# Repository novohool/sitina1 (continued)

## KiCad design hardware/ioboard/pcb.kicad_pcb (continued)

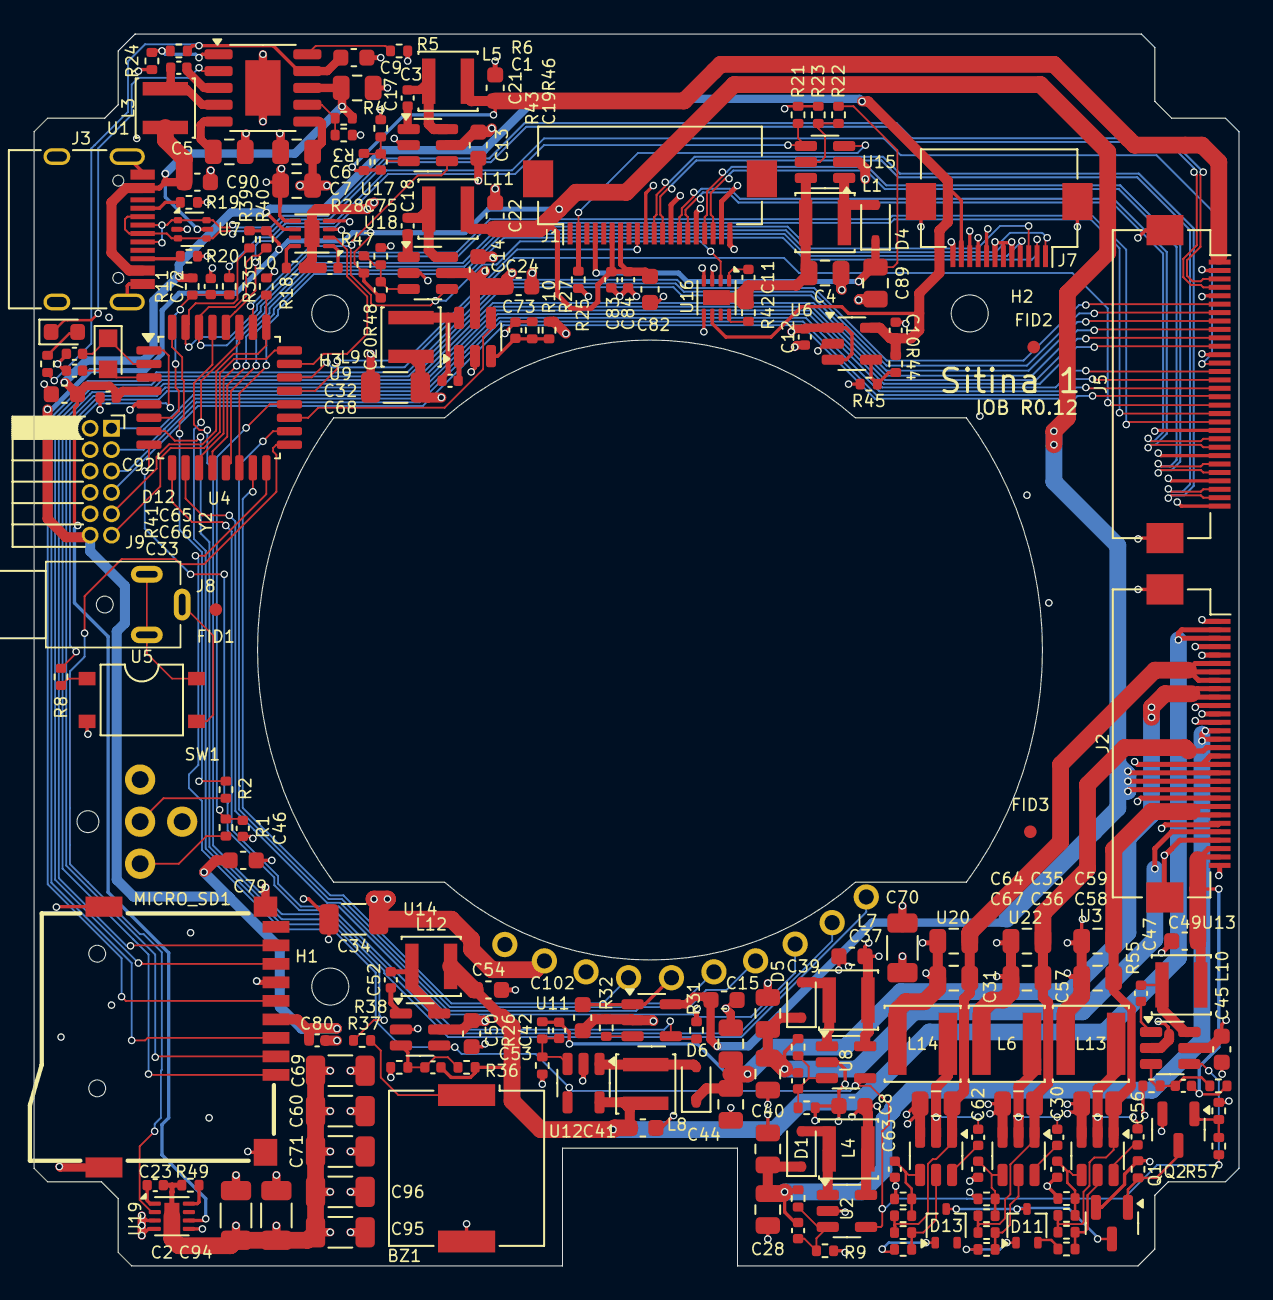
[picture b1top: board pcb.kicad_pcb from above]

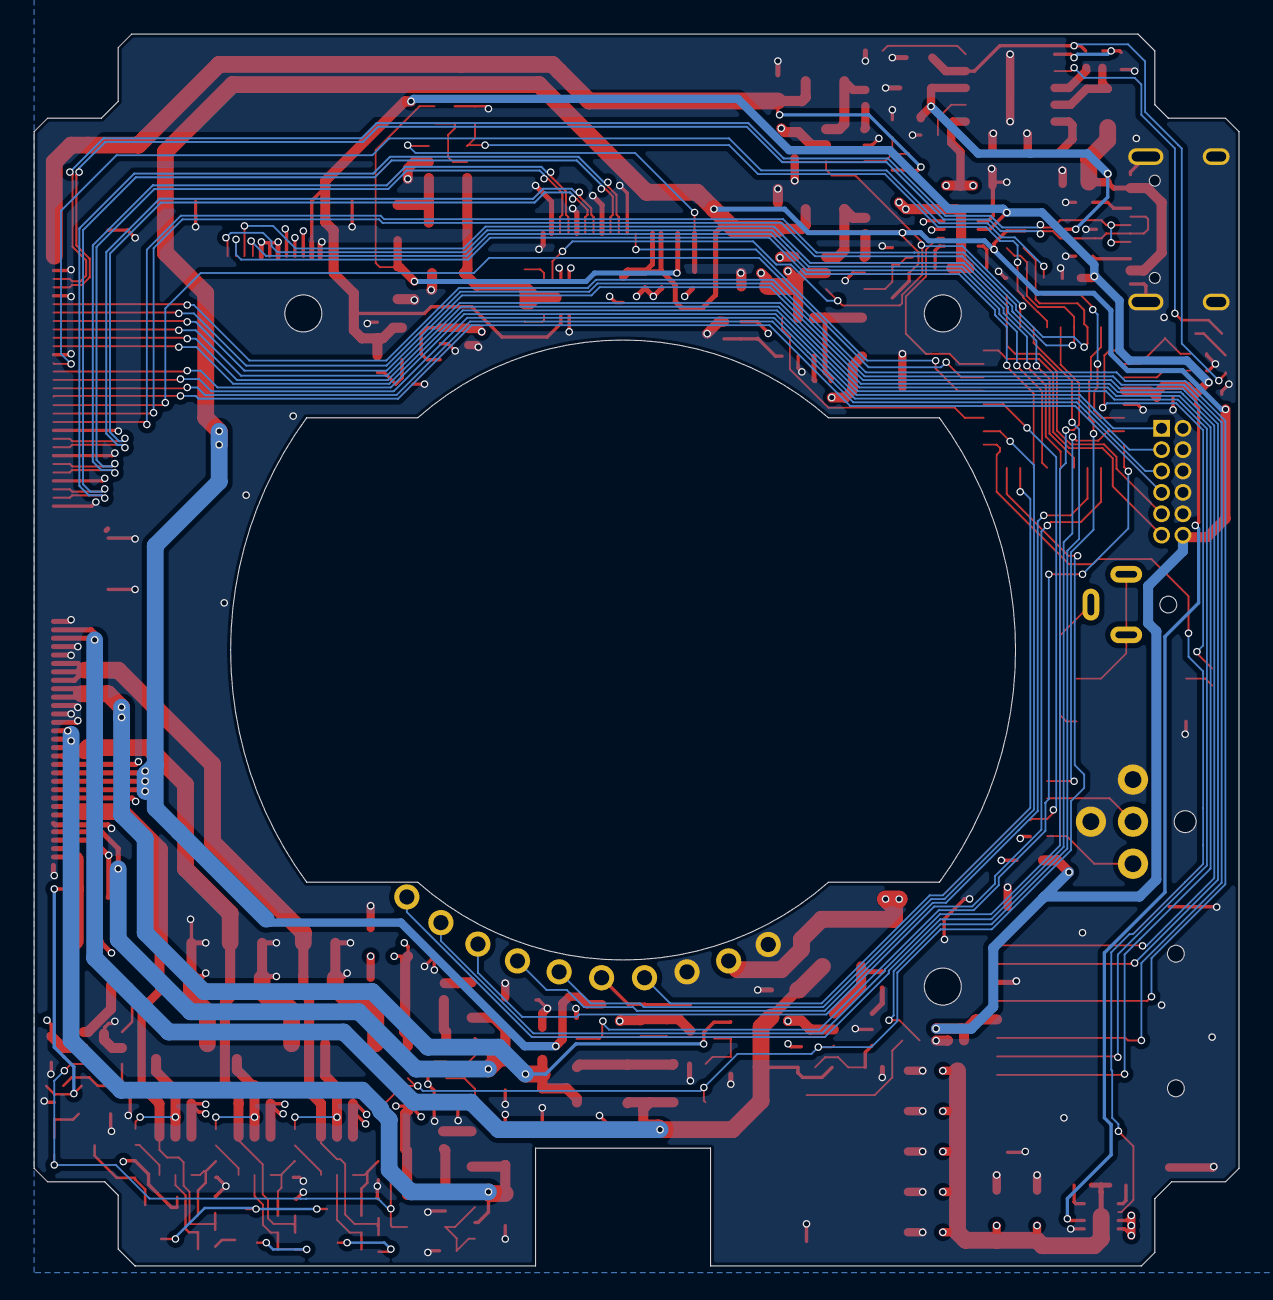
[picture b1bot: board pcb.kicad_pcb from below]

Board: 4 copper layers, 71.6 x 73.2 mm, 212 parts (10 on the bottom side), 135 nets.

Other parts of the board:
MICRO_SD1: MICRO_SD(TFC-WPAPR-08); TFC-WPAPR-08

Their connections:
+3V3: MICRO_SD1.4 (VDD); also elsewhere on the board
GND: MICRO_SD1.6 (VSS), MICRO_SD1.10, MICRO_SD1.11, MICRO_SD1.12, MICRO_SD1.13; also elsewhere on the board
SDIO_CLK: MICRO_SD1.5 (CLK/SCLK); also elsewhere on the board
SDIO_CMD: MICRO_SD1.3 (CMD/DI); also elsewhere on the board
SDIO_DAT0: MICRO_SD1.7 (DAT0/DO); also elsewhere on the board
SDIO_DAT1: MICRO_SD1.8 (DAT1/RES); also elsewhere on the board
SDIO_DAT2: MICRO_SD1.1 (DAT2/RES); also elsewhere on the board
SDIO_DAT3: MICRO_SD1.2 (CD/DAT3/CS); also elsewhere on the board

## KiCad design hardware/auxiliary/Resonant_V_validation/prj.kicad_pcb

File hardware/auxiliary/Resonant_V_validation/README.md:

# Resonant-Mode V Driver Validation Board

## References:
* Michael A. Wyatt, Reactive CCD drive saves power, EDN Magazine, Jan 19, 1999. [EEVBlog Forum](https://www.eevblog.com/forum/projects/reactive-clock-driver-circuit/)

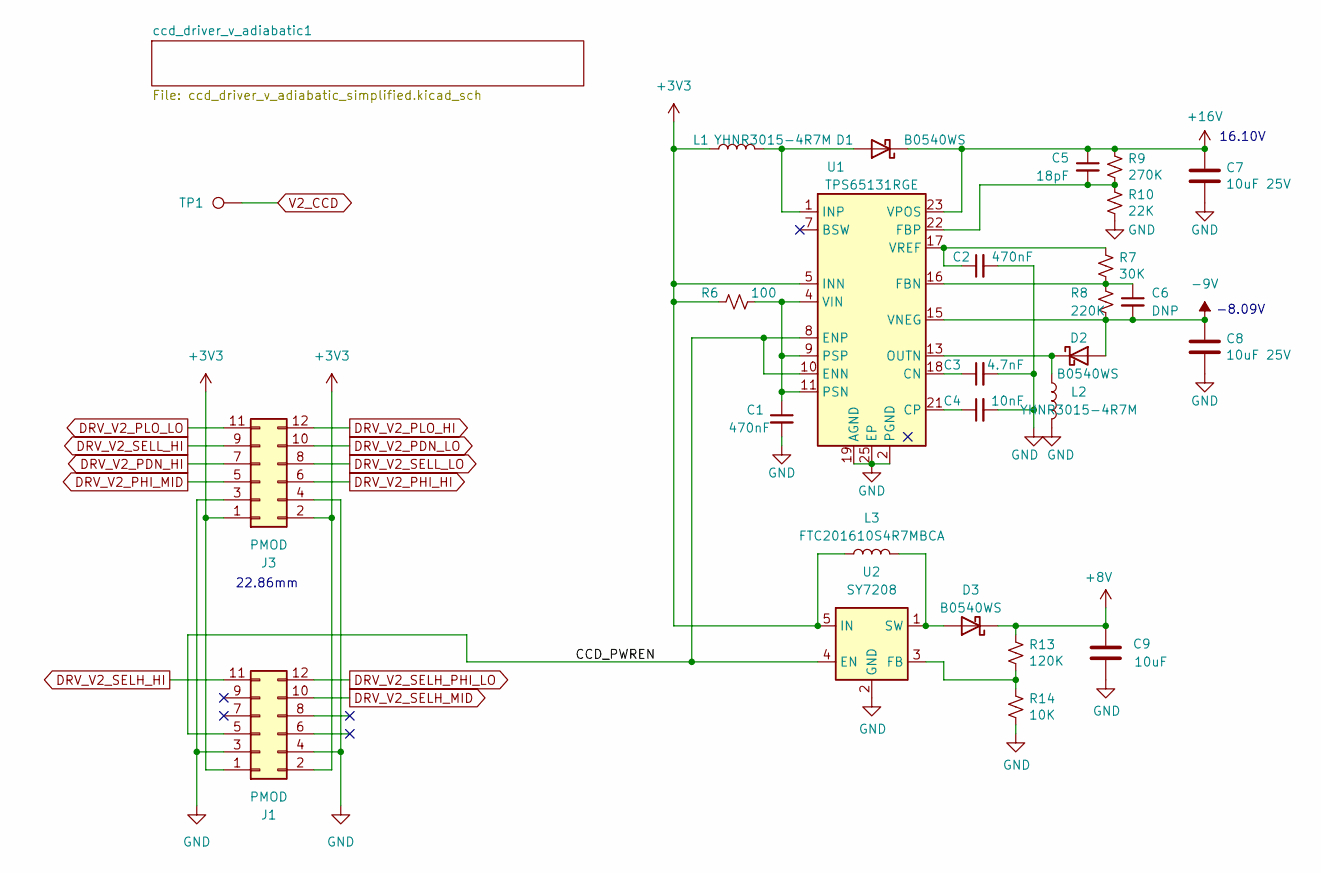
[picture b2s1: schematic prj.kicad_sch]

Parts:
C1, C2: 470nF; C_0402_1005Metric
C3: 4.7nF; C_0402_1005Metric
C4: 10nF; C_0402_1005Metric
C5: 18pF; C_0402_1005Metric
C6: DNP; C_0402_1005Metric
C7, C8: 10uF 25V; C_0805_2012Metric
C9: 10uF; C_0603_1608Metric
D1, D2, D3: B0540WS; D_SOD-323
J1, J3: PMOD; PinHeader_2x06_P2.54mm_Horizontal
L1, L2: YHNR3015-4R7M; L_Changjiang_FNR3015S
L3: FTC201610S4R7MBCA; L_Murata_DFE201610P
R6: 100; R_0402_1005Metric
R7: 30K; R_0402_1005Metric
R8: 220K; R_0402_1005Metric
R9: 270K; R_0402_1005Metric
R10: 22K; R_0402_1005Metric
R13: 120K; R_0402_1005Metric
R14: 10K; R_0402_1005Metric
TP1: TestPoint; TestPoint_Loop_D1.80mm_Drill1.0mm_Beaded
U1: TPS65131RGE; VQFN-24-1EP_4x4mm_P0.5mm_EP2.45x2.45mm_0.3ThermalVias
U2: SY7208; SOT-23-6

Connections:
+3V3: J1.1, J1.2, J3.1, J3.2, L1.2, L3.1, R6.2, U1.5 (INN), U1.6 (INN), U2.5 (IN); also elsewhere on the board
+8V: C9.2, D3.1 (K), R13.1; also elsewhere on the board
+16V: C5.1, C7.1, D1.1 (K), R9.1, U1.23 (VPOS); also elsewhere on the board
-9V: C6.2, C8.1, D2.2 (A), R8.2, U1.15 (VNEG); also elsewhere on the board
/CCD_PWREN: J1.5, U1.8 (ENP), U1.10 (ENN), U2.4 (EN)
DRV_V2_PDN_HI: J3.7; also elsewhere on the board
DRV_V2_PDN_LO: J3.10; also elsewhere on the board
DRV_V2_PHI_HI: J3.6; also elsewhere on the board
DRV_V2_PHI_MID: J3.5; also elsewhere on the board
DRV_V2_PLO_HI: J3.12; also elsewhere on the board
DRV_V2_PLO_LO: J3.11; also elsewhere on the board
DRV_V2_SELH_HI: J1.11; also elsewhere on the board
DRV_V2_SELH_MID: J1.10; also elsewhere on the board
DRV_V2_SELH_PHI_LO: J1.12; also elsewhere on the board
DRV_V2_SELL_HI: J3.9; also elsewhere on the board
DRV_V2_SELL_LO: J3.8; also elsewhere on the board
GND: C1.2, C2.2, C3.2, C4.2, C7.2, C8.2, C9.1, J1.3, J1.4, J3.3, J3.4, L2.1, R10.2, R14.2, U1.2 (PGND), U1.3 (PGND), U1.19 (AGND), U1.25 (EP), U2.2 (GND); also elsewhere on the board
unnamed: D1.2 (A), L1.1, U1.1 (INP), U1.24 (INP)
unnamed: D2.1 (K), L2.2, U1.13 (OUTN), U1.14 (OUTN)
unnamed: D3.2 (A), L3.2, U2.1 (SW)
unnamed: C3.1, U1.18 (CN)
unnamed: C4.1, U1.21 (CP)
unnamed: C6.1, R7.2, R8.1, U1.16 (FBN)
unnamed: C5.2, R9.2, R10.1, U1.22 (FBP)
unnamed: C1.1, R6.1, U1.4 (VIN), U1.9 (PSP), U1.11 (PSN)
unnamed: C2.1, R7.1, U1.17 (VREF)
unnamed: R13.2, R14.1, U2.3 (FB)
V2_CCD: TP1.1; also elsewhere on the board

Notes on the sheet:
-8.09V
16.10V
22.86mm

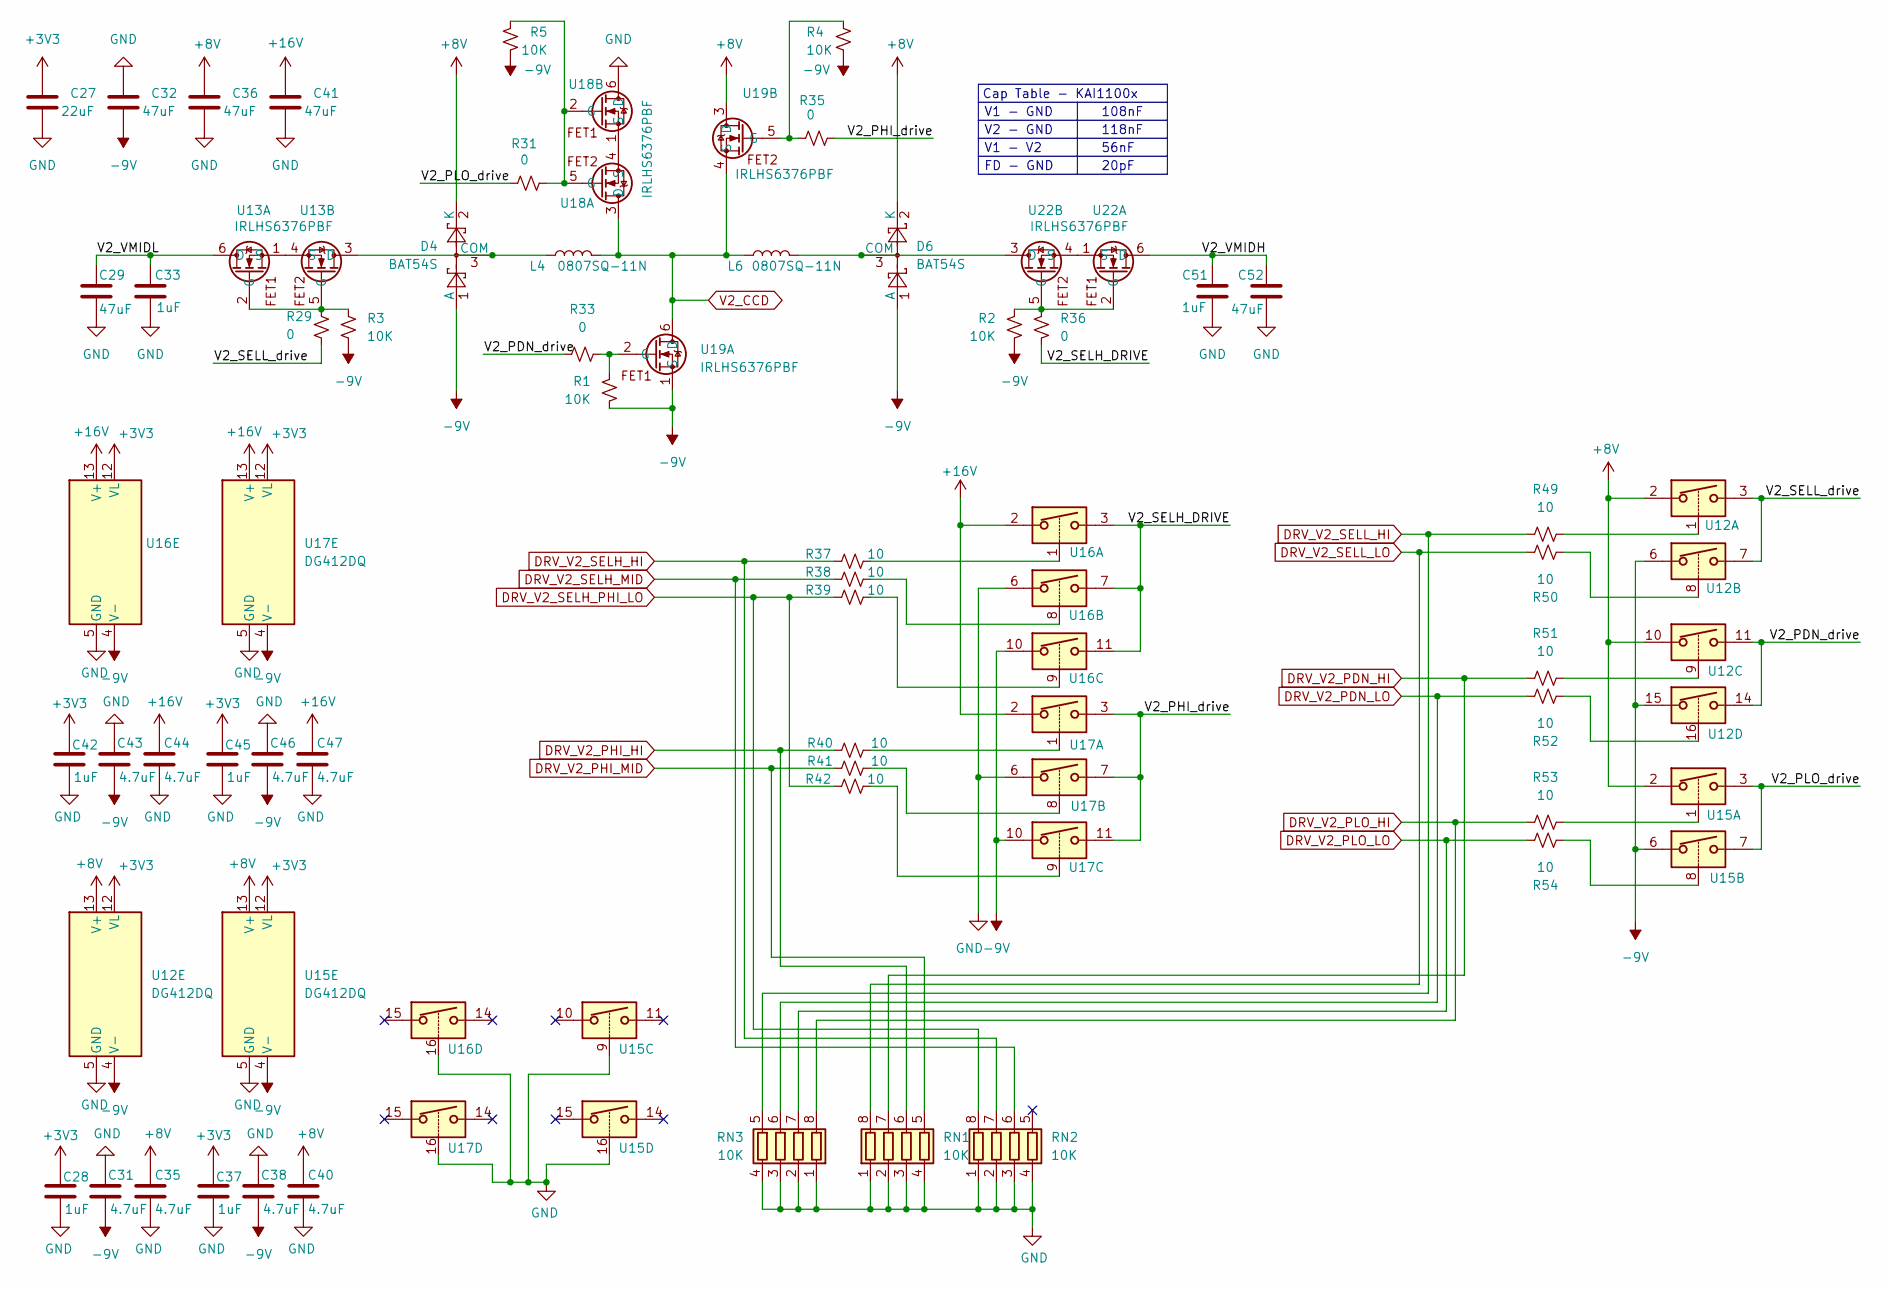
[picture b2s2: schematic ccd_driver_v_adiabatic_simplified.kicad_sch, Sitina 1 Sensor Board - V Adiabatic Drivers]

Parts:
C27: 22uF; C_0805_2012Metric
C28, C37, C42, C45: 1uF; C_0402_1005Metric
C29, C32, C36, C41, C52: 47uF; C_0805_2012Metric
C31, C35, C38, C40, C43, C44, C46, C47: 4.7uF; C_0603_1608Metric
C33, C51: 1uF; C_0603_1608Metric
D4, D6: BAT54S; SOT-23
L4, L6: 0807SQ-11N; Coilcraft_0807SQ-11N
R1, R2, R3, R4, R5: 10K; R_0402_1005Metric
R29, R31, R33, R35, R36: 0; R_0402_1005Metric
R37, R38, R39, R40, R41, R42, R49, R50, R51, R52, R53, R54: 10; R_0402_1005Metric
RN1, RN2, RN3: 10K; R_Array_Concave_4x0402
U12, U15, U16, U17: DG412DQ; TSSOP-16_4.4x5mm_P0.65mm
U13, U18, U19, U22: IRLHS6376PBF; DFN-6-1EP_2x2mm_P0.65mm_EP1.01x1.7mm

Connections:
+3V3: C27.2, C28.2, C37.2, C42.2, C45.2, U12.12 (VL), U15.12 (VL), U16.12 (VL), U17.12 (VL); also elsewhere on the board
+8V: C35.2, C36.2, C40.2, D4.2 (K), D6.2 (K), U12.2, U12.10, U12.13 (V+), U15.2, U15.13 (V+), U19.3 (D); also elsewhere on the board
+16V: C41.2, C44.2, C47.2, U16.2, U16.13 (V+), U17.2, U17.13 (V+); also elsewhere on the board
-9V: C31.1, C32.1, C38.1, C43.1, C46.1, D4.1 (A), D6.1 (A), R1.1, R2.1, R3.1, R4.1, R5.1, U12.4 (V-), U12.6, U12.15, U15.4 (V-), U15.6, U16.4 (V-), U16.10, U17.4 (V-), U17.10, U19.1 (S); also elsewhere on the board
/ccd_driver_v_adiabatic1/V2_PDN_drive: R33.1, U12.11, U12.14
/ccd_driver_v_adiabatic1/V2_PHI_drive: R35.1, U17.3, U17.7, U17.11
/ccd_driver_v_adiabatic1/V2_PLO_drive: R31.2, U15.3, U15.7
/ccd_driver_v_adiabatic1/V2_SELH_DRIVE: R36.2, U16.3, U16.7, U16.11
/ccd_driver_v_adiabatic1/V2_SELL_drive: R29.2, U12.3, U12.7
/ccd_driver_v_adiabatic1/V2_VMIDH: C51.1, C52.1, U22.6 (D)
/ccd_driver_v_adiabatic1/V2_VMIDL: C29.1, C33.1, U13.6 (D)
DRV_V2_PDN_HI: R51.1, RN1.7 (R2.2); also elsewhere on the board
DRV_V2_PDN_LO: R52.2, RN3.6 (R3.2); also elsewhere on the board
DRV_V2_PHI_HI: R40.1, RN1.6 (R3.2); also elsewhere on the board
DRV_V2_PHI_MID: R41.2, RN1.5 (R4.2); also elsewhere on the board
DRV_V2_PLO_HI: R53.1, RN3.8 (R1.2); also elsewhere on the board
DRV_V2_PLO_LO: R54.2, RN3.7 (R2.2); also elsewhere on the board
DRV_V2_SELH_HI: R37.1, RN2.7 (R2.2); also elsewhere on the board
DRV_V2_SELH_MID: R38.2, RN2.6 (R3.2); also elsewhere on the board
DRV_V2_SELH_PHI_LO: R39.2, R42.2, RN2.8 (R1.2); also elsewhere on the board
DRV_V2_SELL_HI: R49.1, RN3.5 (R4.2); also elsewhere on the board
DRV_V2_SELL_LO: R50.2, RN1.8 (R1.2); also elsewhere on the board
GND: C27.1, C28.1, C29.2, C31.2, C32.2, C33.2, C35.1, C36.1, C37.1, C38.2, C40.1, C41.1, C42.1, C43.2, C44.1, C45.1, C46.2, C47.1, C51.2, C52.2, RN1.1 (R1.1), RN1.2 (R2.1), RN1.3 (R3.1), RN1.4 (R4.1), RN2.1 (R1.1), RN2.2 (R2.1), RN2.3 (R3.1), RN2.4 (R4.1), RN3.1 (R1.1), RN3.2 (R2.1), RN3.3 (R3.1), RN3.4 (R4.1), U12.5 (GND), U15.5 (GND), U15.9, U15.16, U16.5 (GND), U16.6, U16.16, U17.5 (GND), U17.6, U17.16, U18.6 (D); also elsewhere on the board
unnamed: D4.3 (COM), L4.1, U13.3 (D)
unnamed: D6.3 (COM), L6.2, U22.3 (D)
unnamed: R37.2, U16.1
unnamed: R38.1, U16.8
unnamed: R39.1, U16.9
unnamed: R40.2, U17.1
unnamed: R41.1, U17.8
unnamed: R42.1, U17.9
unnamed: R49.2, U12.1
unnamed: R50.1, U12.8
unnamed: R51.2, U12.9
unnamed: R52.1, U12.16
unnamed: R53.2, U15.1
unnamed: R54.1, U15.8
unnamed: R3.2, R29.1, U13.2 (G), U13.5 (G)
unnamed: U13.1 (S), U13.4 (S)
unnamed: R5.2, R31.1, U18.2 (G), U18.5 (G)
unnamed: U18.1 (S), U18.4 (S)
unnamed: R1.2, R33.2, U19.2 (G)
unnamed: R4.2, R35.2, U19.5 (G)
unnamed: R2.2, R36.1, U22.2 (G), U22.5 (G)
unnamed: U22.1 (S), U22.4 (S)
V2_CCD: L4.2, L6.1, U18.3 (D), U19.4 (S), U19.6 (D); also elsewhere on the board

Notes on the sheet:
118nF
V1 - V2
Cap Table - KAI1100x
108nF
FD - GND
56nF
V2 - GND
20pF
V1 - GND

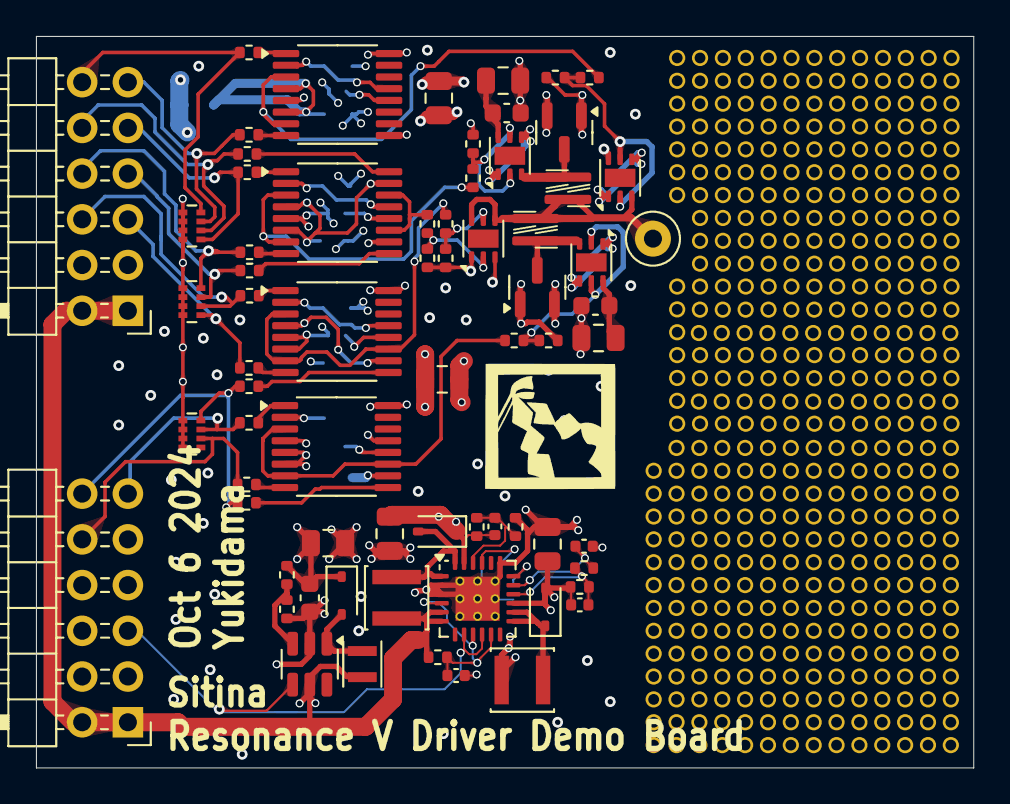
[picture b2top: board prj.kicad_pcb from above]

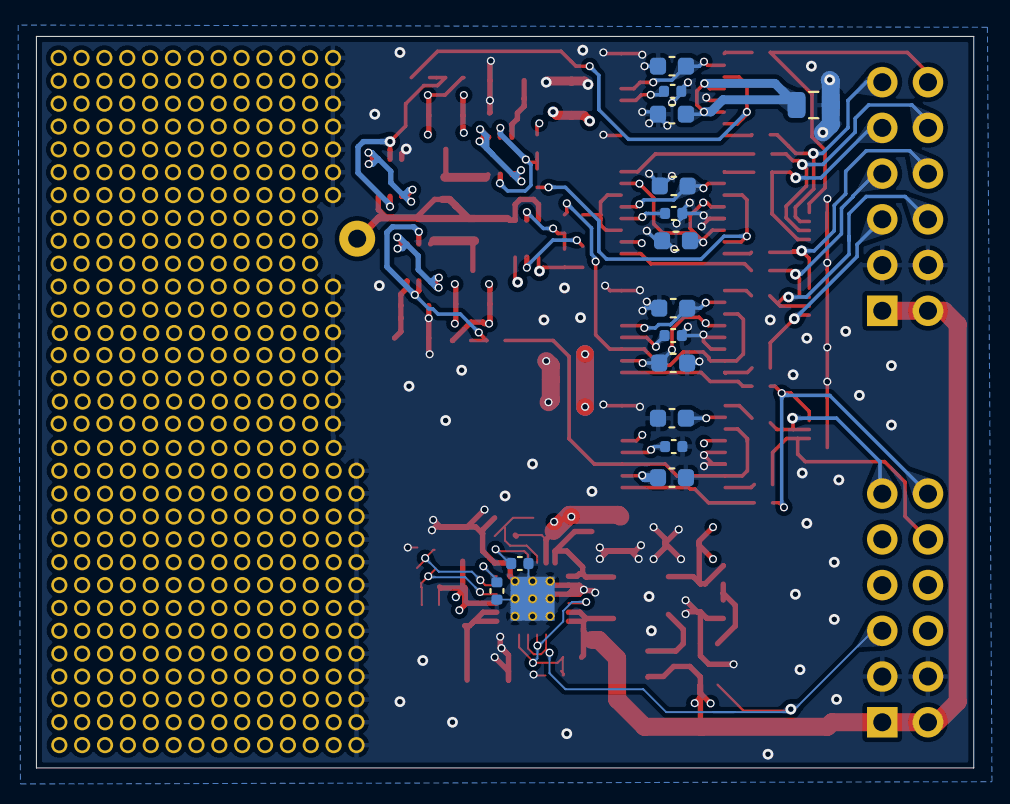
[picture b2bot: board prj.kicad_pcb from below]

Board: 4 copper layers, 52.1 x 40.6 mm, 84 parts (15 on the bottom side), 57 nets.

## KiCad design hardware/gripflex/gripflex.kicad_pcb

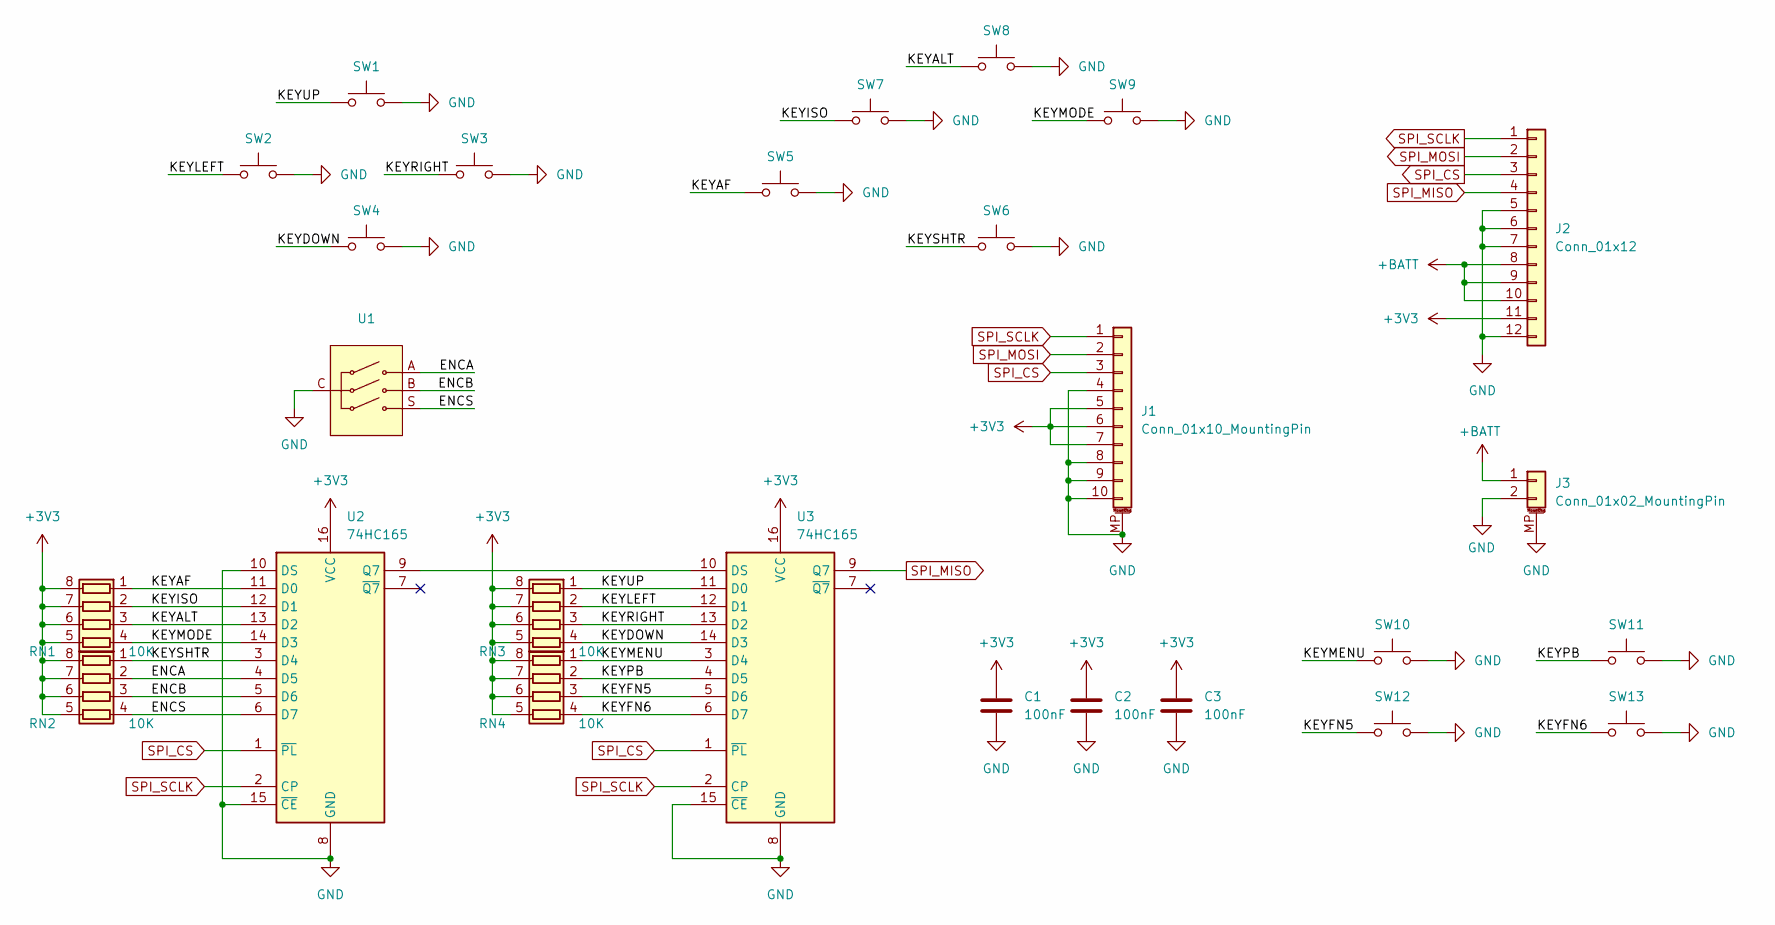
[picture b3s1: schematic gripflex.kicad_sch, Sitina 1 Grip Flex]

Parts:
C1, C2, C3: 100nF; C_0402_1005Metric
J1: Conn_01x10_MountingPin; Hirose_FH12-10S-0.5SH_1x10-1MP_P0.50mm_Horizontal
J2: Conn_01x12; FPC_12
J3: Conn_01x02_MountingPin; JST_PH_S2B-PH-SM4-TB_1x02-1MP_P2.00mm_Horizontal
RN1, RN2, RN3, RN4: 10K; R_Array_Convex_4x0402
SW1, SW2, SW3, SW4, SW5, SW6, SW7, SW8, SW9, SW10, SW11, SW12, SW13: HX-TS5208A
U1: SIQ-02FVS3_L
U2, U3: 74HC165; TSSOP-16_4.4x5mm_P0.65mm

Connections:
+3V3: C1.1, C2.1, C3.1, J1.5, J1.6, J1.7, J2.11, RN1.5 (R4.2), RN1.6 (R3.2), RN1.7 (R2.2), RN1.8 (R1.2), RN2.5 (R4.2), RN2.6 (R3.2), RN2.7 (R2.2), RN2.8 (R1.2), RN3.5 (R4.2), RN3.6 (R3.2), RN3.7 (R2.2), RN3.8 (R1.2), RN4.5 (R4.2), RN4.6 (R3.2), RN4.7 (R2.2), RN4.8 (R1.2), U2.16 (VCC), U3.16 (VCC)
+BATT: J2.8, J2.9, J2.10, J3.1
/ENCA: RN2.2 (R2.1), U1.A, U2.4 (D5)
/ENCB: RN2.3 (R3.1), U1.B, U2.5 (D6)
/ENCS: RN2.4 (R4.1), U1.S, U2.6 (D7)
/KEYAF: RN1.1 (R1.1), SW5.1, U2.11 (D0)
/KEYALT: RN1.3 (R3.1), SW8.1, U2.13 (D2)
/KEYDOWN: RN3.4 (R4.1), SW4.1, U3.14 (D3)
/KEYFN5: RN4.3 (R3.1), SW12.1, U3.5 (D6)
/KEYFN6: RN4.4 (R4.1), SW13.1, U3.6 (D7)
/KEYISO: RN1.2 (R2.1), SW7.1, U2.12 (D1)
/KEYLEFT: RN3.2 (R2.1), SW2.1, U3.12 (D1)
/KEYMENU: RN4.1 (R1.1), SW10.1, U3.3 (D4)
/KEYMODE: RN1.4 (R4.1), SW9.1, U2.14 (D3)
/KEYPB: RN4.2 (R2.1), SW11.1, U3.4 (D5)
/KEYRIGHT: RN3.3 (R3.1), SW3.1, U3.13 (D2)
/KEYSHTR: RN2.1 (R1.1), SW6.1, U2.3 (D4)
/KEYUP: RN3.1 (R1.1), SW1.1, U3.11 (D0)
GND: C1.2, C2.2, C3.2, J1.4, J1.8, J1.9, J1.10, J1.MP (MountPin), J2.5, J2.6, J2.7, J2.12, J3.2, J3.MP (MountPin), SW1.2, SW2.2, SW3.2, SW4.2, SW5.2, SW6.2, SW7.2, SW8.2, SW9.2, SW10.2, SW11.2, SW12.2, SW13.2, U1.C, U2.8 (GND), U2.10 (DS), U2.15 (~CE), U3.8 (GND), U3.15 (~CE)
unnamed: U2.9 (Q7), U3.10 (DS)
SPI_CS: J1.3, J2.3, U2.1 (~PL), U3.1 (~PL)
SPI_MISO: J2.4, U3.9 (Q7)
SPI_MOSI: J1.2, J2.2
SPI_SCLK: J1.1, J2.1, U2.2 (CP), U3.2 (CP)

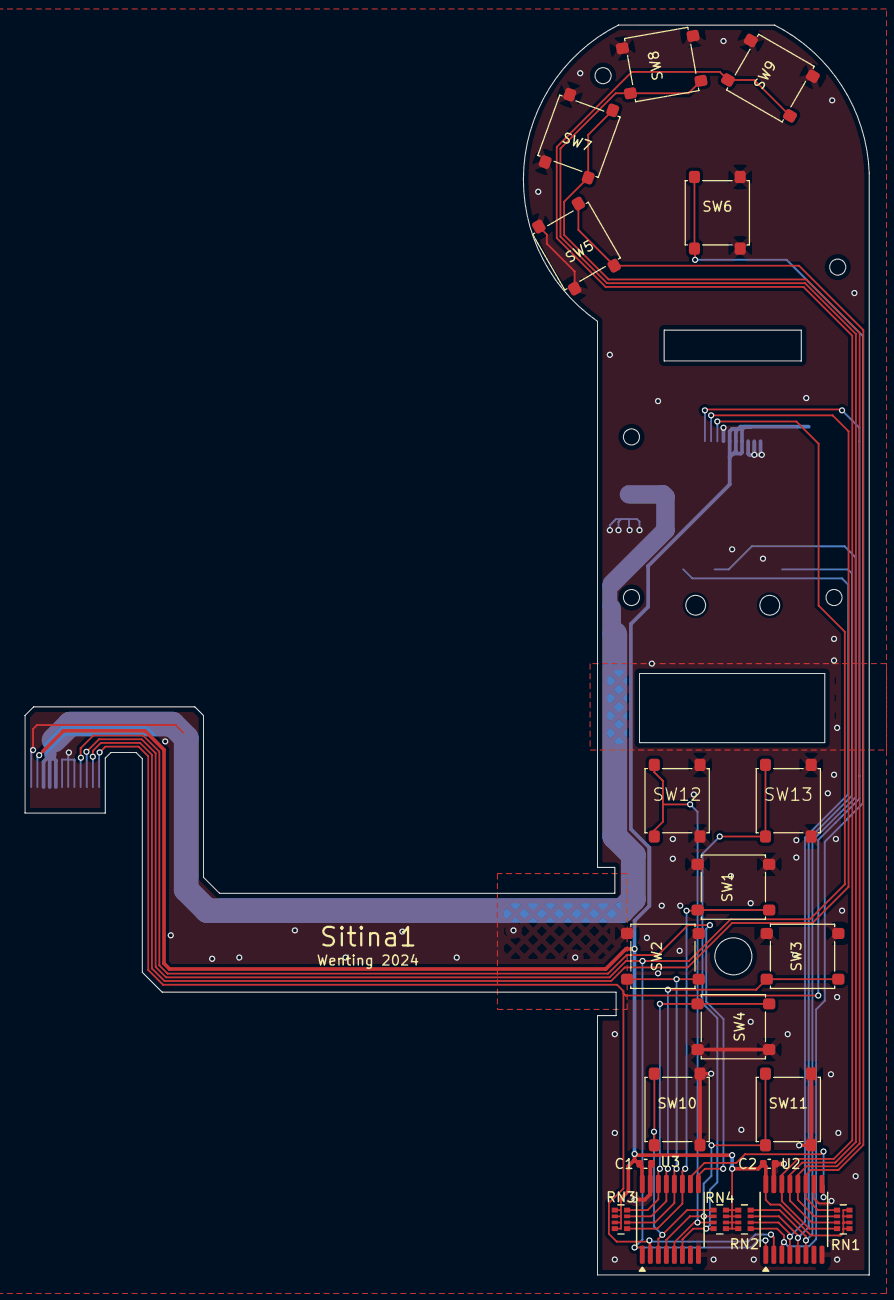
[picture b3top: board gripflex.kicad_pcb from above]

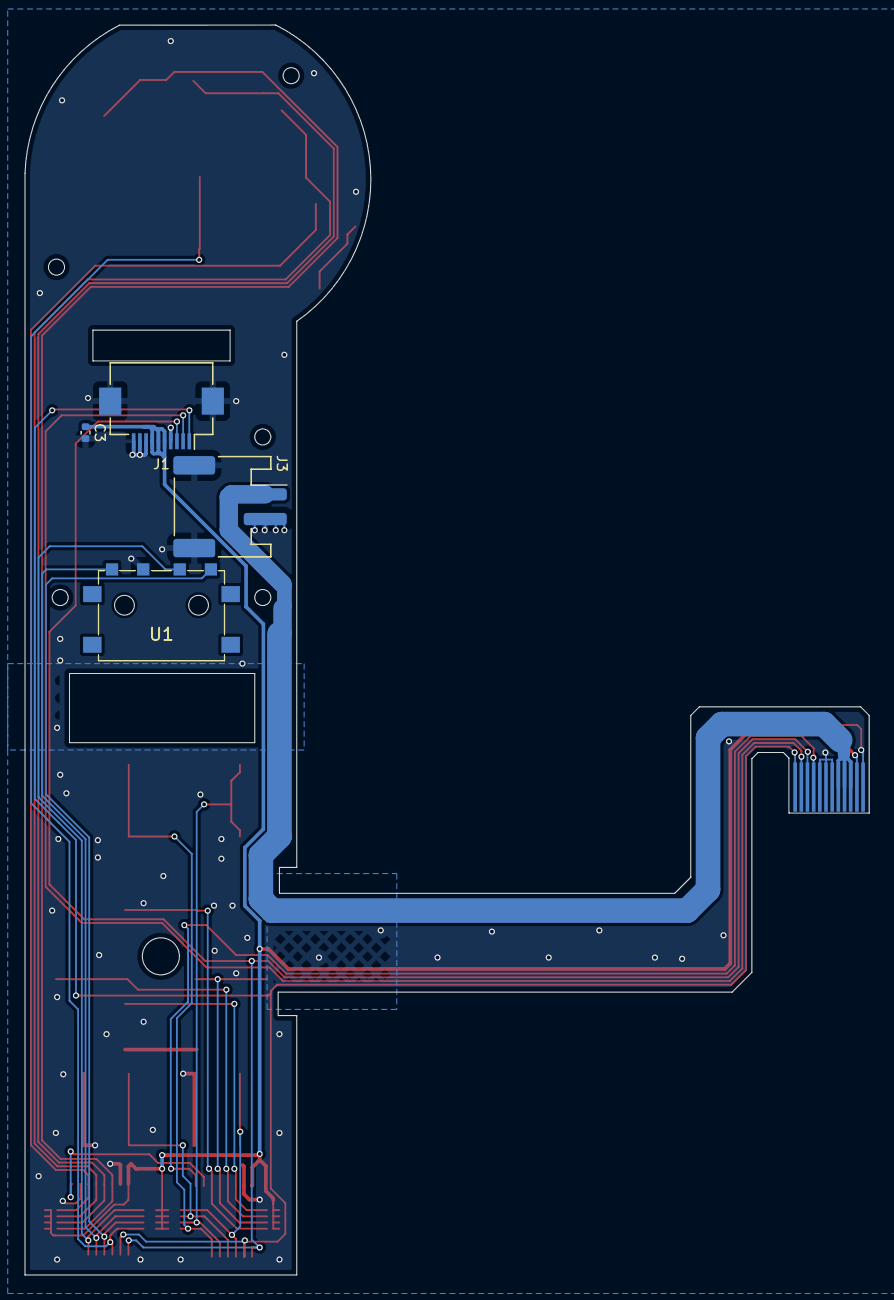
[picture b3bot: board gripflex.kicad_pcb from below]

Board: 2 copper layers, 68.3 x 101.2 mm, 26 parts (5 on the bottom side), 24 nets.

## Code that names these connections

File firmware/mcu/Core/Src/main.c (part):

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  /*Configure GPIO pin Output Level */
  HAL_GPIO_WritePin(GPIOA, GPIO_PIN_1|GPIO_PIN_4, GPIO_PIN_RESET);

  /*Configure GPIO pins : PB9 PB0 PB1 PB2
                           PB5 PB6 PB7 PB8 */
  GPIO_InitStruct.Pin = GPIO_PIN_9|GPIO_PIN_0|GPIO_PIN_1|GPIO_PIN_2
                          |GPIO_PIN_5|GPIO_PIN_6|GPIO_PIN_7|GPIO_PIN_8;
  GPIO_InitStruct.Mode = GPIO_MODE_OUTPUT_PP;
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  GPIO_InitStruct.Speed = GPIO_SPEED_FREQ_LOW;
  HAL_GPIO_Init(GPIOB, &GPIO_InitStruct);

  /*Configure GPIO pins : PA0 PA8 PA15 */
  GPIO_InitStruct.Pin = GPIO_PIN_0|GPIO_PIN_8|GPIO_PIN_15;
  GPIO_InitStruct.Mode = GPIO_MODE_INPUT;
  GPIO_InitStruct.Pull = GPIO_NOPULL;
  HAL_GPIO_Init(GPIOA, &GPIO_InitStruct);

  /*Configure GPIO pins : PA1 PA4 */
  GPIO_InitStruct.Pin = GPIO_PIN_1|GPIO_PIN_4;
  GPIO_InitStruct.Mode = GPIO_MODE_OUTPUT_PP;
  GPIO_InitStruct.Pull = GPIO_NOPULL;
  GPIO_InitStruct.Speed = GPIO_SPEED_FREQ_LOW;
  HAL_GPIO_Init(GPIOA, &GPIO_InitStruct);

  /*Configure GPIO pins : PA2 PA3 */
  GPIO_InitStruct.Pin = GPIO_PIN_2|GPIO_PIN_3;
  GPIO_InitStruct.Mode = GPIO_MODE_AF_PP;
  GPIO_InitStruct.Pull = GPIO_NOPULL;
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  GPIO_InitStruct.Alternate = GPIO_AF1_USART2;
  HAL_GPIO_Init(GPIOA, &GPIO_InitStruct);

  /*Configure GPIO pin : PB3 */
  GPIO_InitStruct.Pin = GPIO_PIN_3;
  GPIO_InitStruct.Mode = GPIO_MODE_AF_PP;
  GPIO_InitStruct.Pull = GPIO_NOPULL;
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
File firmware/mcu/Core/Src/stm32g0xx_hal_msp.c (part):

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
    __HAL_RCC_GPIOA_CLK_ENABLE();
    /**I2C1 GPIO Configuration
    PA9     ------> I2C1_SCL
    PA10     ------> I2C1_SDA
    */
    GPIO_InitStruct.Pin = GPIO_PIN_9|GPIO_PIN_10;
    GPIO_InitStruct.Mode = GPIO_MODE_AF_OD;
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
    __HAL_RCC_GPIOA_CLK_ENABLE();
    /**I2C2 GPIO Configuration
    PA11 [PA9]     ------> I2C2_SCL
    PA12 [PA10]     ------> I2C2_SDA
    */
    GPIO_InitStruct.Pin = GPIO_PIN_11|GPIO_PIN_12;
    GPIO_InitStruct.Mode = GPIO_MODE_AF_OD;
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    __HAL_RCC_I2C1_CLK_DISABLE();

    /**I2C1 GPIO Configuration
    PA9     ------> I2C1_SCL
    PA10     ------> I2C1_SDA
    */
    HAL_GPIO_DeInit(GPIOA, GPIO_PIN_9);

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    __HAL_RCC_I2C2_CLK_DISABLE();

    /**I2C2 GPIO Configuration
    PA11 [PA9]     ------> I2C2_SCL
    PA12 [PA10]     ------> I2C2_SDA
    */
    HAL_GPIO_DeInit(GPIOA, GPIO_PIN_11);

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
    __HAL_RCC_GPIOA_CLK_ENABLE();
    /**SPI1 GPIO Configuration
    PA5     ------> SPI1_SCK
    PA6     ------> SPI1_MISO
    PA7     ------> SPI1_MOSI
    */
    GPIO_InitStruct.Pin = GPIO_PIN_5|GPIO_PIN_6|GPIO_PIN_7;
    GPIO_InitStruct.Mode = GPIO_MODE_AF_PP;
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    __HAL_RCC_SPI1_CLK_DISABLE();

    /**SPI1 GPIO Configuration
    PA5     ------> SPI1_SCK
    PA6     ------> SPI1_MISO
    PA7     ------> SPI1_MOSI
    */
    HAL_GPIO_DeInit(GPIOA, GPIO_PIN_5|GPIO_PIN_6|GPIO_PIN_7);

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
    __HAL_RCC_GPIOB_CLK_ENABLE();
    /**TIM3 GPIO Configuration
    PB4     ------> TIM3_CH1
    */
    GPIO_InitStruct.Pin = GPIO_PIN_4;
    GPIO_InitStruct.Mode = GPIO_MODE_AF_PP;
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
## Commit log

2024-10-10 'cahnge'
